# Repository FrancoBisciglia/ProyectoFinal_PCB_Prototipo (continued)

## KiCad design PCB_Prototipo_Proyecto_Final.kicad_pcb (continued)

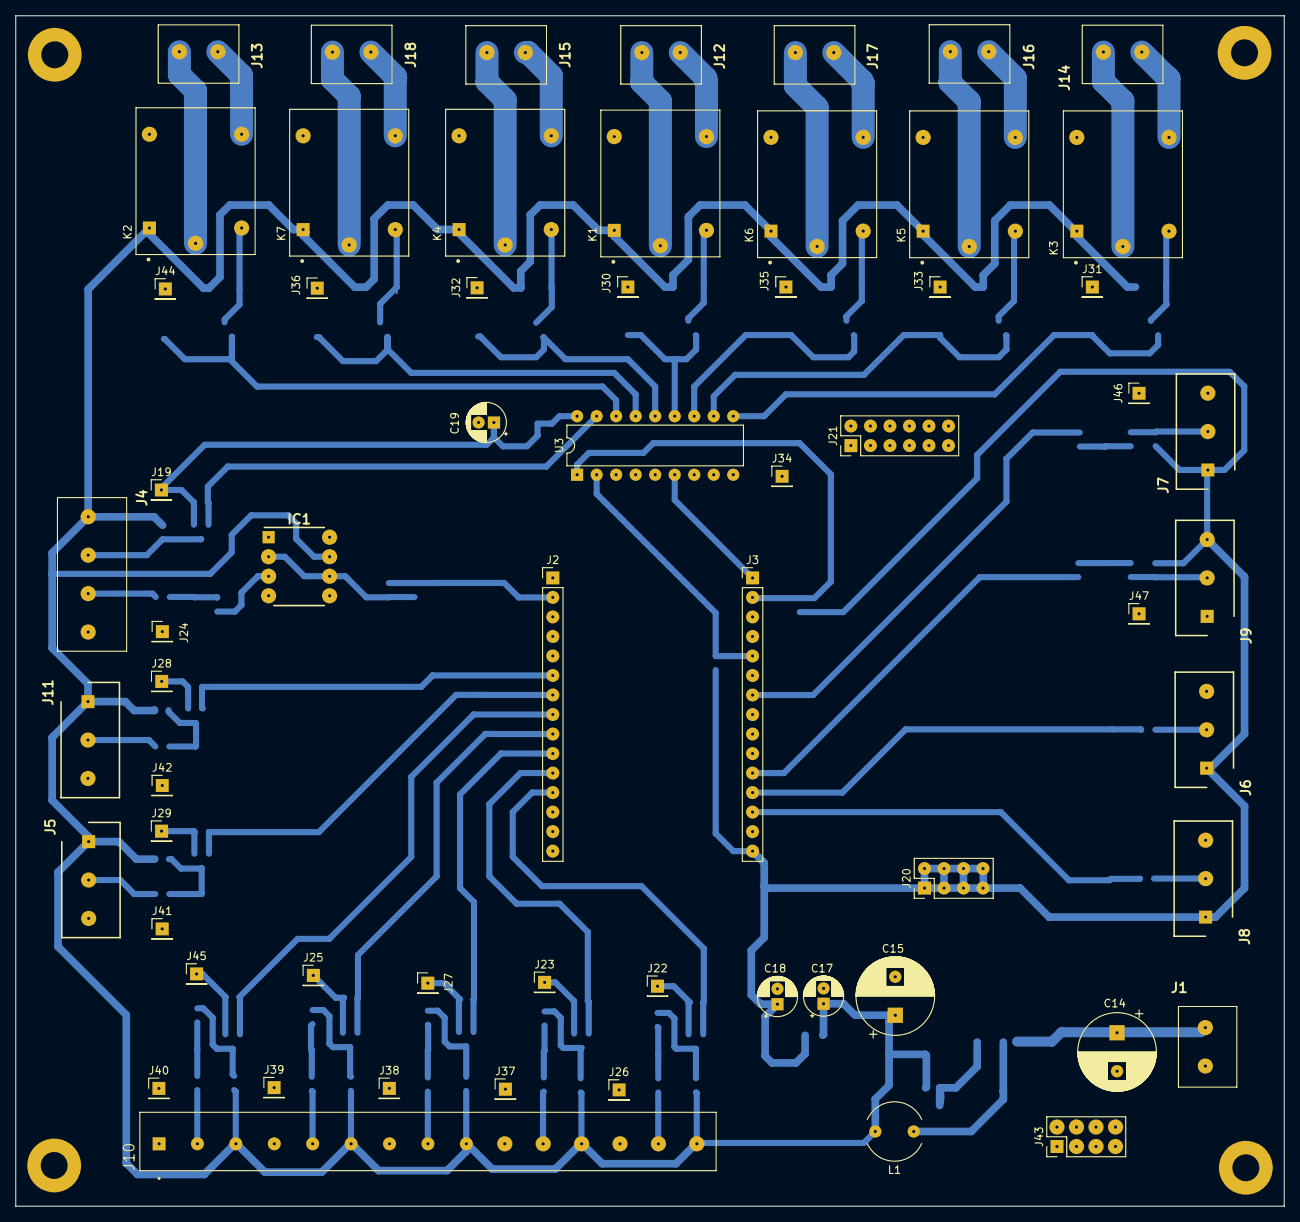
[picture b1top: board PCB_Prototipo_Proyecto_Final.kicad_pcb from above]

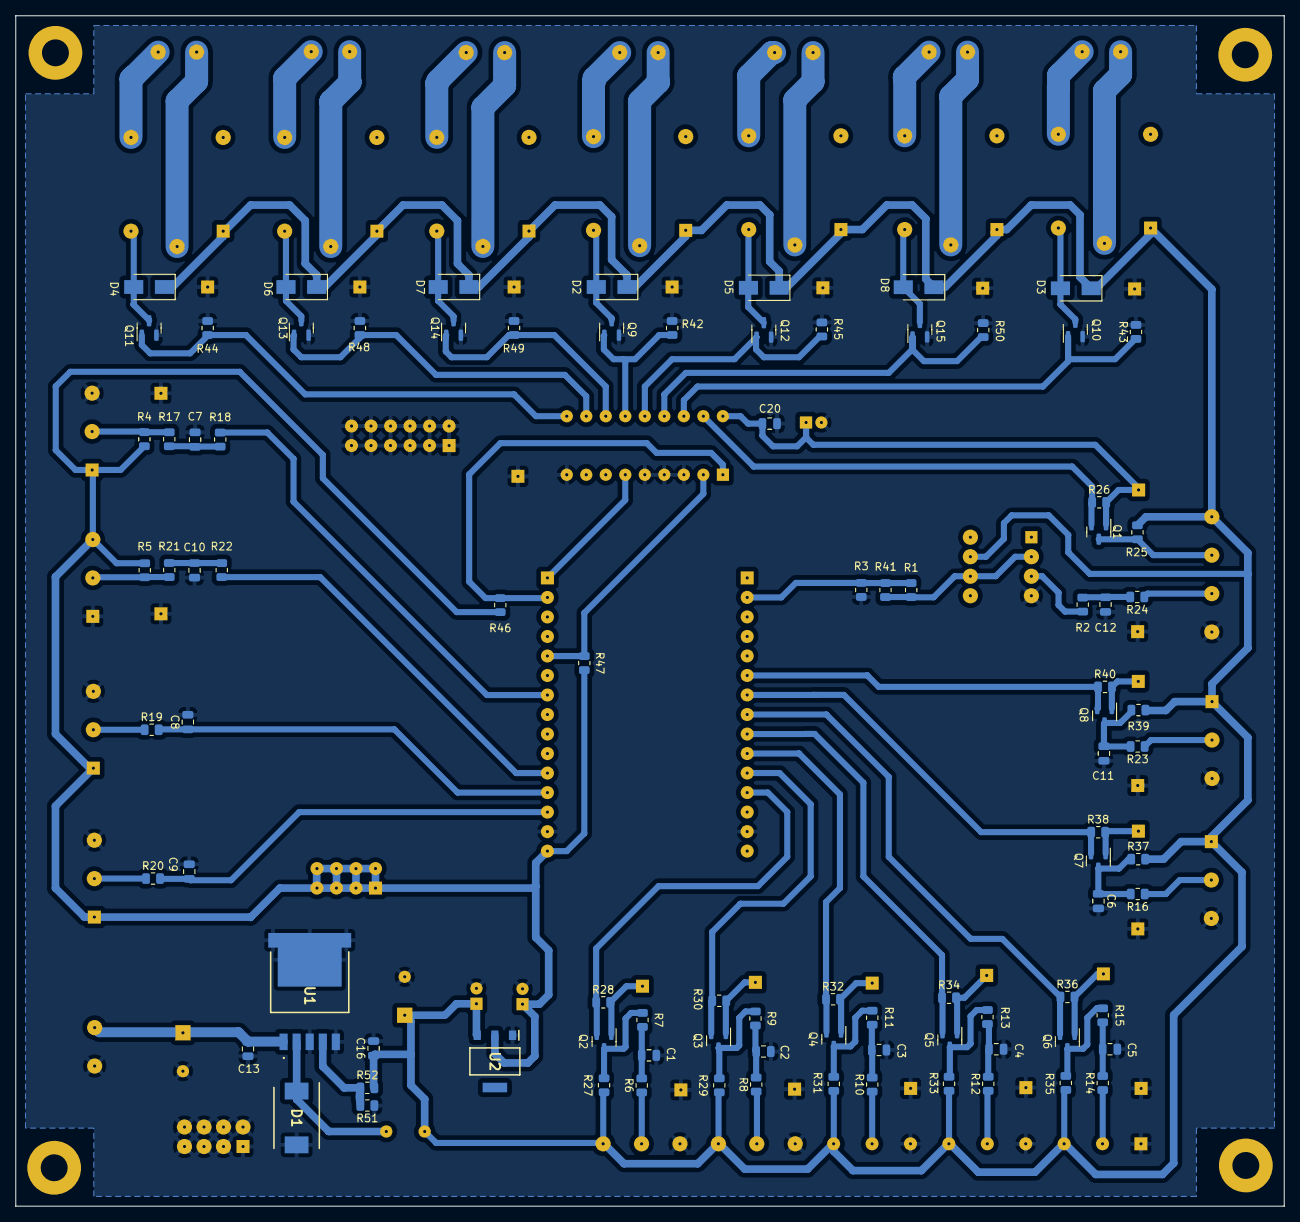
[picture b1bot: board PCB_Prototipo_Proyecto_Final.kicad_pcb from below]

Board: 2 copper layers, 165.1 x 154.9 mm, 154 parts (92 on the bottom side), 80 nets.

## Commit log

2022-09-23 Carga inicial de archivos
2022-09-23 Ajuste del esquematico
    Se cambio el integrado ESP32 por 2 tiras de pines de 1x15, se quitaron los switches EN y BOOT que ya estan en el NodeMCU, se quito el mutliplexor 74HC y se cablearon las I/O
2022-09-24 Subida de backups
2022-09-24 Modificación de posición de circ. filtrado y circ. de adaptación de tensión
2022-09-24 Corrección de errores menores de esquematico
2022-10-01 Actualización de SCH según placa industrial, y búsqueda de footprints.
2022-10-03 Fin de SCH, config de inicio para PCB
2022-10-03 Inicio de trazado de PCB
    Se empezaron a acomodar los footprints.
2022-10-07 Cambios en SCH y PCB.
    Se cambio el adaptador de nivel 5-3,3V por un circuito con MOSFET 2N7002, dado que ya no hay stock del NXB. Se modificó el footprint del expansor I/O por uno thorugh-hole.
2022-10-07 Continuación de trazado de PCB.
2022-10-09 Se finalizó con el PCB del prototipo.
    Dado que se buscó a toda costa que el PCB fuera de 1 capa, en varios puntos del circuito se tuvieron que agregar pin headers individuales para conectar a 3V3 y GND, junto con tiras de pin headers. Ca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
    Tambien se generaron los archivos Gerber y BOM.
2022-10-13 Se modificaron los footprints del capacitor de 470 uF y del LM1117.
2022-10-13 Actualización.
2022-10-14 Se modificaron algunos componentes, según disponibilidad
2022-10-15 Modificación de componentes.
    Se agregó al PCB los footprints de los componentes que se cambiaron según la disponibilidad que había (resistencias, transistor de los relés, diodo de los reles)
2022-10-15 Se cambiaron todos los componentes a la capa BOTTOM.
2022-10-16 Modificacion de PCB.
    Me di cuenta que, al pasar los componentes SMD y las pistas al lado BOTTOM, los componentes TH quedaron todos al revés, por lo que será necesario rediseñar la PCB para acomodarlos del lado TOP correc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
2022-10-17 Inicio de rerouteo.
2022-10-17 Continuación de rerouteo.
2022-10-17 Finalización de rerouteo de PCB.
2022-10-20 Actualización de backups.
2022-10-21 Correccion footprints
    Se realizo el cambio de algunas footprints segun los componentes disponibles, como los capacitores de 470 uF o la inductancia de la fte switching, y tambien se cambio el LM2596 por el modelo ADJ, con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
2022-10-22 Corrección de PCB.
    Se agregaron algunos pin headers para conectar a GND algunos puntos. Se generaron los Gerber finales.
2022-10-24 Actualizacion de backups
2022-10-24 Modificación de footprint del MCP23008
    Se lo modifico de forma de poder utilizar el adaptador SOP/PDIP, ya que tiene un ancho de 1,5 cm, que es más grande que el PDIP solo.
2022-10-24 Generación de Gerber y Drill files.
2022-10-24 Generación de Gerbers y Drill
2022-10-24 Actualización de PCB y regeneración de Gerbers y Drill
2022-10-27 Corrección de errores menores de pistas.
2022-10-27 Corrección de errores menores en pistas de PCB.
2022-11-01 Corrección de errores menores y generación de Gerbers.
2022-11-01 Generación de Gerbers.
2023-03-13 Cambios modelos 3D.
2023-03-13 Modificaciones modelo 3D.
